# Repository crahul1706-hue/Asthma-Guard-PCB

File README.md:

# Asthma Guard – ESP32 Sensor Interface PCB

## Project Overview
This project focuses on designing a PCB for the Asthma Guard system, which monitors environmental air quality using sensors connected to an ESP32 microcontroller.

## Objectives
- Interface environmental sensors with the ESP32.
- Organize sensor connections on a dedicated PCB.
- Support the development of a portable air-quality monitoring system.

## Hardware Components
- ESP32 DevKit
- MQ-135 air-quality sensor
- DHT22 temperature and humidity sensor
- PM2.5 particulate matter sensor

## Design Tools
- KiCad – schematic capture and PCB layout
- Gerber files – PCB fabrication data

## Repository Structure
- `KiCad_Project/` – KiCad schematic, PCB layout, and project settings
- `Gerber_Files/` – exported Gerber files for PCB fabrication

## Project Status
PCB design files and Gerber exports are organized in this repository.

## Future Improvements
- Verify footprints and component pin mappings.
- Complete design-rule and manufacturing checks.
- Test the PCB with the connected sensors and ESP32.

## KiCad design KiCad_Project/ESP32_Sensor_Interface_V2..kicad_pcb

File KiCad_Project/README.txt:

Asthma Guard – KiCad Project Files

This folder contains the KiCad design files for the Asthma Guard ESP32 Sensor Interface PCB.

**Files included:**
- `.kicad_pcb` – PCB layout
- `.kicad_sch` – Circuit schematic
- `.kicad_pro` – KiCad project settings

Software used: KiCad

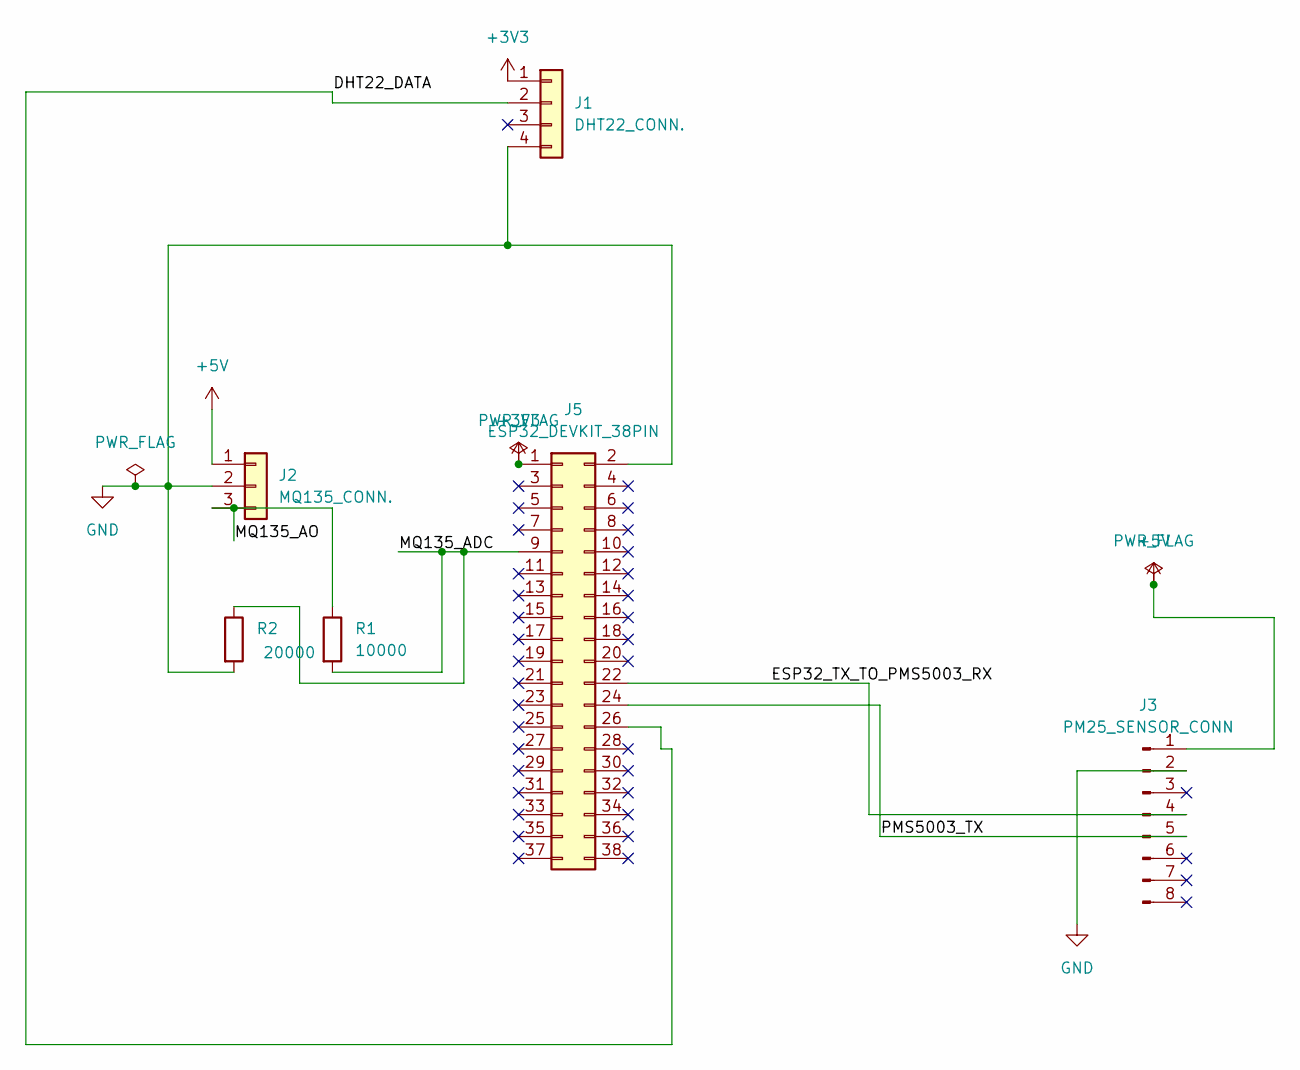
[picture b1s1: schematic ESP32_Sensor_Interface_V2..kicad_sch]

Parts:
J1: DHT22_CONN.; FanPinHeader_1x04_P2.54mm_Vertical
J2: MQ135_CONN.; PinHeader_1x03_P2.54mm_Vertical
J3: PM25_SENSOR_CONN; PinHeader_1x08_P2.54mm_Vertical
J5: ESP32_DEVKIT_38PIN; PinHeader_2x19_P2.54mm_Vertical
R1: 10000; R_Axial_DIN0207_L6.3mm_D2.5mm_P7.62mm_Horizontal
R2: 20000; R_Axial_DIN0207_L6.3mm_D2.5mm_P7.62mm_Horizontal

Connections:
+3V3: J1.1, J5.1
+5V: J2.1, J3.1
/DHT22_DATA: J1.2, J5.26
/ESP32_TX_TO_PMS5003_RX: J3.4, J5.22
/MQ135_ADC: J5.9, R1.2, R2.1
/MQ135_AO: J2.3, R1.1
/PMS5003_TX: J3.5, J5.24
GND: J1.4, J2.2, J3.2, J5.2, R2.2

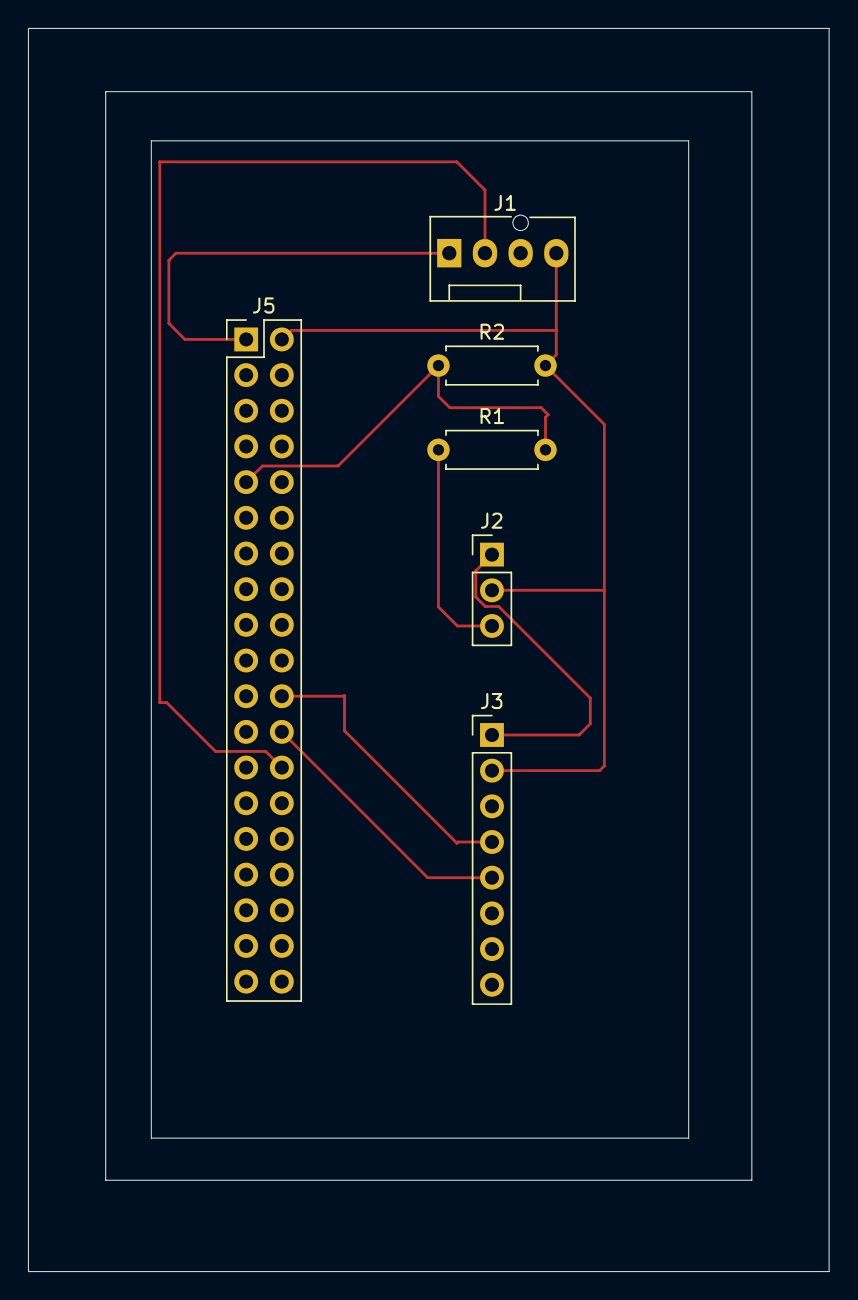
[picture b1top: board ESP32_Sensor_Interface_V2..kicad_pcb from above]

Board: 2 copper layers, 57.0 x 88.5 mm, 6 parts (0 on the bottom side), 8 nets.
